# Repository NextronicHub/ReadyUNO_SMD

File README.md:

# ReadyUNO_SMD
## Description
READY-UNO is the best board to start your personal electronics projects, it is built upon the famous ARDUINO UNO, so it shares its simplicity and its flexibility. It contains also a BreadBoard with different interfaces of communication (SPI, UART, I2C and Serial communication) for easy development.
The READY-UNO can be programmed over a Serial Communication, using the ARDUINO IDE.
The READY-UNO can be powered through the barrel jack. The on-board power regulator can handle anything from 7 to 15VDC.
## Features
•	ATmega328 microcontroller with Optiboot (UNO) Bootloader                                                                         
•	Input voltage : 7 to 15V                                                                                                         
•	0-5V outputs                                                                                                                     
•	14 Digital I/O Pins (6 PWM outputs)                                                                                              
•	6 Analog Inputs                                                                                                                  
•	ISP Header                                                                                                                       
•	32k Flash Memory                                                                                                                 
•	16MHz Clock Speed                                                                                                                
•	All SMD Construction                                                                                                             
•	R3 Shield Compatible                                                                                                             
•	BreadBoard.                                                                                                                      
•	Red PCB.                                                                                                                         
•	I2C, UART and SPI.                                                                                                               
## Repository Contents

/Hardware - Design files (.brd, .sch)  
/Firmware - bootloader
/Documentation - datasheet and examples

## Product Versions

ReadyUNO-SMD-V1 first release

## License Information

The hardware is released under [Creative Commons ShareAlike 4.0 International](https://creativecommons.org/licenses/by-sa/4.0/).

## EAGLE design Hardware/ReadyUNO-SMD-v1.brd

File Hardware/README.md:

# Nextronic ReadyUNO_SMD Design Files
The .sch and .brd files are Eagle CAD schematic and PCB design files from Nextronic. Eagle PCB Design | Schematic Editor, Layout Editor & Autorouter can be found at http://www.autodesk.com/products/eagle.

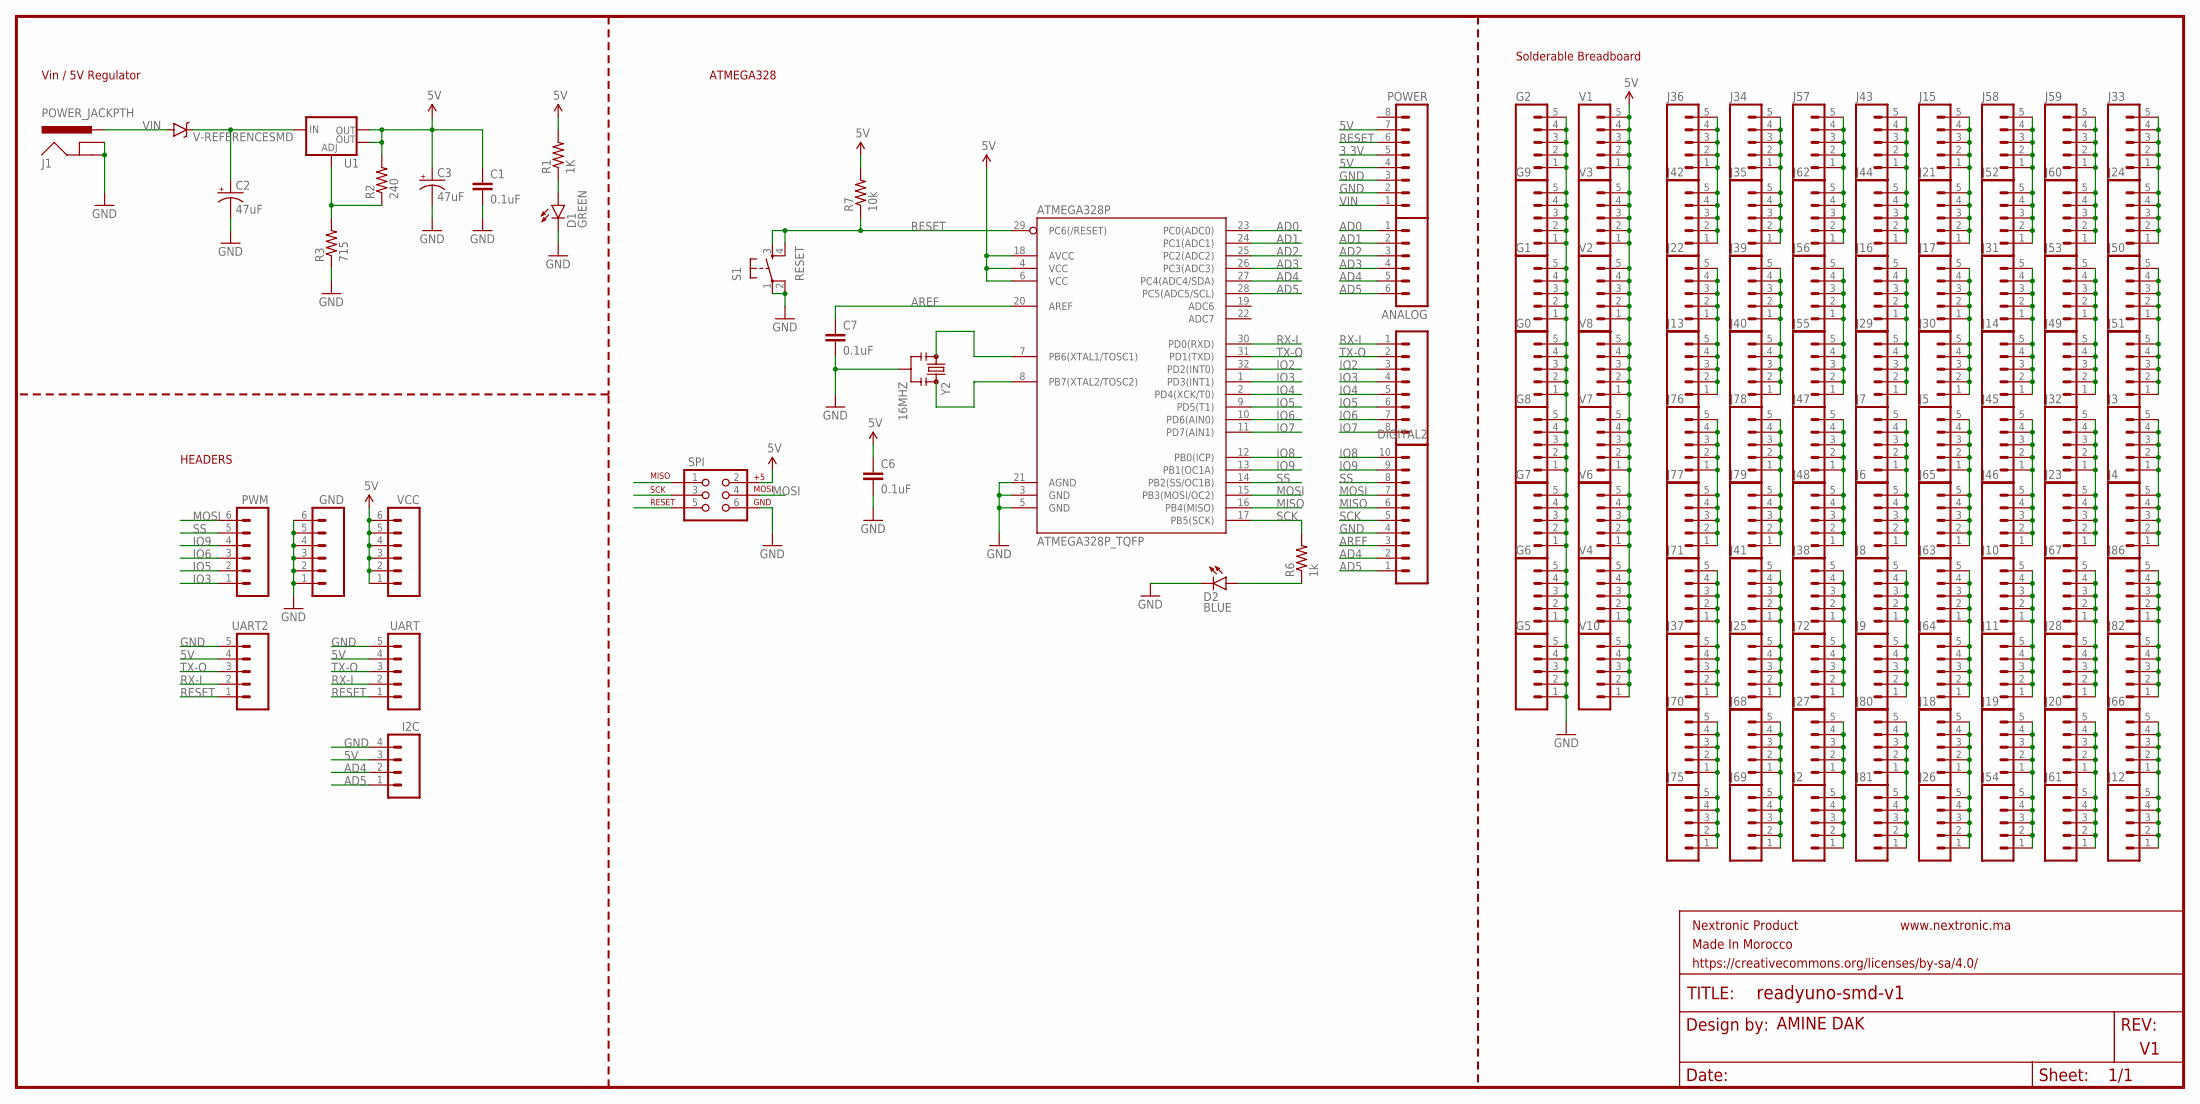
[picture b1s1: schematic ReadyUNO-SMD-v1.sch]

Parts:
ANALOG: M06SILK_FEMALE_PTH; 1X06
ATMEGA328P: ATMEGA328P_TQFP; TQFP32-08
C1, C6, C7: 0.1uF; 0603-CAP
C2, C3: 47uF; PANASONIC_C
D1: GREEN; LED-1206
D2: BLUE; LED-1206
DIGITAL: M08SILK_FEMALE_PTH; 1X08
DIGITAL2: M10SILK_FEMALE_PTH; 1X10
G0, G1, G2, G5, G6, G7, G8, G9: M05PTH; 1X05
GND: M06SILK_FEMALE_PTH; 1X06
I2C: M04PTH; 1X04
J1: POWER_JACKPTH; POWER_JACK_PTH
J2, J3, J4, J5, J6, J7, J8, J9, J10, J11, J12, J13, J14, J15, J16, J17, J18, J19, J20, J21, J22, J23, J24, J25, J26, J27, J28, J29, J30, J31, J32, J33, J34, J35, J36, J37, J38, J39, J40, J41, J42, J43, J44, J45, J46, J47, J48, J49, J50, J51, J52, J53, J54, J55, J56, J57, J58, J59, J60, J61, J62, J63, J64, J65, J66, J67, J68, J69, J70, J71, J72, J75, J76, J77, J78, J79, J80, J81, J82, J86: M05PTH; 1X05
POWER: M08SILK_FEMALE_PTH; 1X08
PWM: M06SILK_FEMALE_PTH; 1X06
R1: 1K; 0603-RES
R2: 240; 0603-RES
R3: 715; 0603-RES
R6: 1k; 0603-RES
R7: 10k; 0603-RES
S1: RESET; TACTILE-SWITCH-SMD
SPI: AVR_SPI_PRG_6NS; 2X3-NS
U1: V_REG_LM1117SOT223; SOT223
U$1: V-REFERENCESMD; SOT23-3
UART, UART2: M05PTH; 1X05
V1, V2, V3, V4, V6, V7, V8, V10: M05PTH; 1X05
VCC: M06SILK_FEMALE_PTH; 1X06
Y2: 16MHZ; RESONATOR-SMD

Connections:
3.3V: POWER.5
5V: ATMEGA328P.4 (VCC), ATMEGA328P.6 (VCC), ATMEGA328P.18 (AVCC), C1.1, C3.+, C6.1, I2C.3, POWER.4, POWER.7, R1.2, R2.2, R7.2, SPI.2, U1.2 (OUT), U1.4 (OUT), UART.4, UART2.4, V1.1, V1.2, V1.3, V1.4, V1.5, V2.1, V2.2, V2.3, V2.4, V2.5, V3.1, V3.2, V3.3, V3.4, V3.5, V4.1, V4.2, V4.3, V4.4, V4.5, V6.1, V6.2, V6.3, V6.4, V6.5, V7.1, V7.2, V7.3, V7.4, V7.5, V8.1, V8.2, V8.3, V8.4, V8.5, V10.1, V10.2, V10.3, V10.4, V10.5, VCC.1, VCC.2, VCC.3, VCC.4, VCC.5, VCC.6
AD0: ANALOG.1, ATMEGA328P.23 (PC0(ADC0))
AD1: ANALOG.2, ATMEGA328P.24 (PC1(ADC1))
AD2: ANALOG.3, ATMEGA328P.25 (PC2(ADC2))
AD3: ANALOG.4, ATMEGA328P.26 (PC3(ADC3))
AD4: ANALOG.5, ATMEGA328P.27 (PC4(ADC4/SDA)), DIGITAL2.2, I2C.2
AD5: ANALOG.6, ATMEGA328P.28 (PC5(ADC5/SCL)), DIGITAL2.1, I2C.1
AREF: ATMEGA328P.20 (AREF), C7.1, DIGITAL2.3
GND: ATMEGA328P.3 (GND), ATMEGA328P.5 (GND), ATMEGA328P.21 (AGND), C1.2, C2.-, C3.-, C6.2, C7.2, D1.C, D2.C, DIGITAL2.4, G0.1, G0.2, G0.3, G0.4, G0.5, G1.1, G1.2, G1.3, G1.4, G1.5, G2.1, G2.2, G2.3, G2.4, G2.5, G5.1, G5.2, G5.3, G5.4, G5.5, G6.1, G6.2, G6.3, G6.4, G6.5, G7.1, G7.2, G7.3, G7.4, G7.5, G8.1, G8.2, G8.3, G8.4, G8.5, G9.1, G9.2, G9.3, G9.4, G9.5, GND.1, GND.2, GND.3, GND.4, GND.5, GND.6, I2C.4, J1.GND, J1.GNDBREAK, POWER.2, POWER.3, R3.1, S1.1, S1.2, SPI.6, UART.5, UART2.5, Y2.2
IO2: ATMEGA328P.32 (PD2(INT0)), DIGITAL.3
IO3: ATMEGA328P.1 (PD3(INT1)), DIGITAL.4, PWM.1
IO4: ATMEGA328P.2 (PD4(XCK/T0)), DIGITAL.5
IO5: ATMEGA328P.9 (PD5(T1)), DIGITAL.6, PWM.2
IO6: ATMEGA328P.10 (PD6(AIN0)), DIGITAL.7, PWM.3
IO7: ATMEGA328P.11 (PD7(AIN1)), DIGITAL.8
IO8: ATMEGA328P.12 (PB0(ICP)), DIGITAL2.10
IO9: ATMEGA328P.13 (PB1(OC1A)), DIGITAL2.9, PWM.4
MISO: ATMEGA328P.16 (PB4(MISO)), DIGITAL2.6, SPI.1
MOSI: ATMEGA328P.15 (PB3(MOSI/OC2)), DIGITAL2.7, PWM.6, SPI.4
unnamed: R2.1, R3.2, U1.1 (ADJ)
unnamed: D2.A, R6.1
unnamed: C2.+, U1.3 (IN), U$1.1 (C)
unnamed: D1.A, R1.1
unnamed: J37.1, J37.2, J37.3, J37.4, J37.5, J71.1, J71.2, J71.3, J71.4, J71.5
unnamed: ATMEGA328P.7 (PB6(XTAL1/TOSC1)), Y2.1
unnamed: ATMEGA328P.8 (PB7(XTAL2/TOSC2)), Y2.3
unnamed: J3.1, J3.2, J3.3, J3.4, J3.5, J4.1, J4.2, J4.3, J4.4, J4.5
unnamed: J10.1, J10.2, J10.3, J10.4, J10.5, J11.1, J11.2, J11.3, J11.4, J11.5
unnamed: J76.1, J76.2, J76.3, J76.4, J76.5, J77.1, J77.2, J77.3, J77.4, J77.5
unnamed: J28.1, J28.2, J28.3, J28.4, J28.5, J67.1, J67.2, J67.3, J67.4, J67.5
unnamed: J25.1, J25.2, J25.3, J25.4, J25.5, J41.1, J41.2, J41.3, J41.4, J41.5
unnamed: J78.1, J78.2, J78.3, J78.4, J78.5, J79.1, J79.2, J79.3, J79.4, J79.5
unnamed: J82.1, J82.2, J82.3, J82.4, J82.5, J86.1, J86.2, J86.3, J86.4, J86.5
unnamed: J45.1, J45.2, J45.3, J45.4, J45.5, J46.1, J46.2, J46.3, J46.4, J46.5
unnamed: J47.1, J47.2, J47.3, J47.4, J47.5, J48.1, J48.2, J48.3, J48.4, J48.5
unnamed: J12.1, J12.2, J12.3, J12.4, J12.5, J66.1, J66.2, J66.3, J66.4, J66.5
unnamed: J20.1, J20.2, J20.3, J20.4, J20.5, J61.1, J61.2, J61.3, J61.4, J61.5
unnamed: J38.1, J38.2, J38.3, J38.4, J38.5, J72.1, J72.2, J72.3, J72.4, J72.5
unnamed: J24.1, J24.2, J24.3, J24.4, J24.5, J33.1, J33.2, J33.3, J33.4, J33.5
unnamed: J23.1, J23.2, J23.3, J23.4, J23.5, J32.1, J32.2, J32.3, J32.4, J32.5
unnamed: J49.1, J49.2, J49.3, J49.4, J49.5, J53.1, J53.2, J53.3, J53.4, J53.5
unnamed: J59.1, J59.2, J59.3, J59.4, J59.5, J60.1, J60.2, J60.3, J60.4, J60.5
unnamed: J14.1, J14.2, J14.3, J14.4, J14.5, J31.1, J31.2, J31.3, J31.4, J31.5
unnamed: J17.1, J17.2, J17.3, J17.4, J17.5, J30.1, J30.2, J30.3, J30.4, J30.5
unnamed: J52.1, J52.2, J52.3, J52.4, J52.5, J58.1, J58.2, J58.3, J58.4, J58.5
unnamed: J50.1, J50.2, J50.3, J50.4, J50.5, J51.1, J51.2, J51.3, J51.4, J51.5
unnamed: J16.1, J16.2, J16.3, J16.4, J16.5, J29.1, J29.2, J29.3, J29.4, J29.5
unnamed: J43.1, J43.2, J43.3, J43.4, J43.5, J44.1, J44.2, J44.3, J44.4, J44.5
unnamed: J15.1, J15.2, J15.3, J15.4, J15.5, J21.1, J21.2, J21.3, J21.4, J21.5
unnamed: J36.1, J36.2, J36.3, J36.4, J36.5, J42.1, J42.2, J42.3, J42.4, J42.5
unnamed: J13.1, J13.2, J13.3, J13.4, J13.5, J22.1, J22.2, J22.3, J22.4, J22.5
unnamed: J6.1, J6.2, J6.3, J6.4, J6.5, J7.1, J7.2, J7.3, J7.4, J7.5
unnamed: J8.1, J8.2, J8.3, J8.4, J8.5, J9.1, J9.2, J9.3, J9.4, J9.5
unnamed: J34.1, J34.2, J34.3, J34.4, J34.5, J35.1, J35.2, J35.3, J35.4, J35.5
unnamed: J39.1, J39.2, J39.3, J39.4, J39.5, J40.1, J40.2, J40.3, J40.4, J40.5
unnamed: J5.1, J5.2, J5.3, J5.4, J5.5, J65.1, J65.2, J65.3, J65.4, J65.5
unnamed: J63.1, J63.2, J63.3, J63.4, J63.5, J64.1, J64.2, J64.3, J64.4, J64.5
unnamed: J57.1, J57.2, J57.3, J57.4, J57.5, J62.1, J62.2, J62.3, J62.4, J62.5
unnamed: J55.1, J55.2, J55.3, J55.4, J55.5, J56.1, J56.2, J56.3, J56.4, J56.5
unnamed: J19.1, J19.2, J19.3, J19.4, J19.5, J54.1, J54.2, J54.3, J54.4, J54.5
unnamed: J80.1, J80.2, J80.3, J80.4, J80.5, J81.1, J81.2, J81.3, J81.4, J81.5
unnamed: J18.1, J18.2, J18.3, J18.4, J18.5, J26.1, J26.2, J26.3, J26.4, J26.5
unnamed: J70.1, J70.2, J70.3, J70.4, J70.5, J75.1, J75.2, J75.3, J75.4, J75.5
unnamed: J2.1, J2.2, J2.3, J2.4, J2.5, J27.1, J27.2, J27.3, J27.4, J27.5
unnamed: J68.1, J68.2, J68.3, J68.4, J68.5, J69.1, J69.2, J69.3, J69.4, J69.5
RESET: ATMEGA328P.29 (PC6(/RESET)), POWER.6, R7.1, S1.3, S1.4, SPI.5, UART.1, UART2.1
RX-I: ATMEGA328P.30 (PD0(RXD)), DIGITAL.1, UART.2, UART2.2
SCK: ATMEGA328P.17 (PB5(SCK)), DIGITAL2.5, R6.2, SPI.3
SS: ATMEGA328P.14 (PB2(SS/OC1B)), DIGITAL2.8, PWM.5
TX-O: ATMEGA328P.31 (PD1(TXD)), DIGITAL.2, UART.3, UART2.3
VIN: J1.PWR, POWER.1, U$1.2 (A)

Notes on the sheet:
Vin / 5V Regulator
ATMEGA328
HEADERS
Solderable Breadboard
AMINE DAK
Date:
Sheet:
REV:
TITLE:
Nextronic Product
Made In Morocco
https://creativecommons.org/licenses/by-sa/4.0/
Design by:
www.nextronic.ma

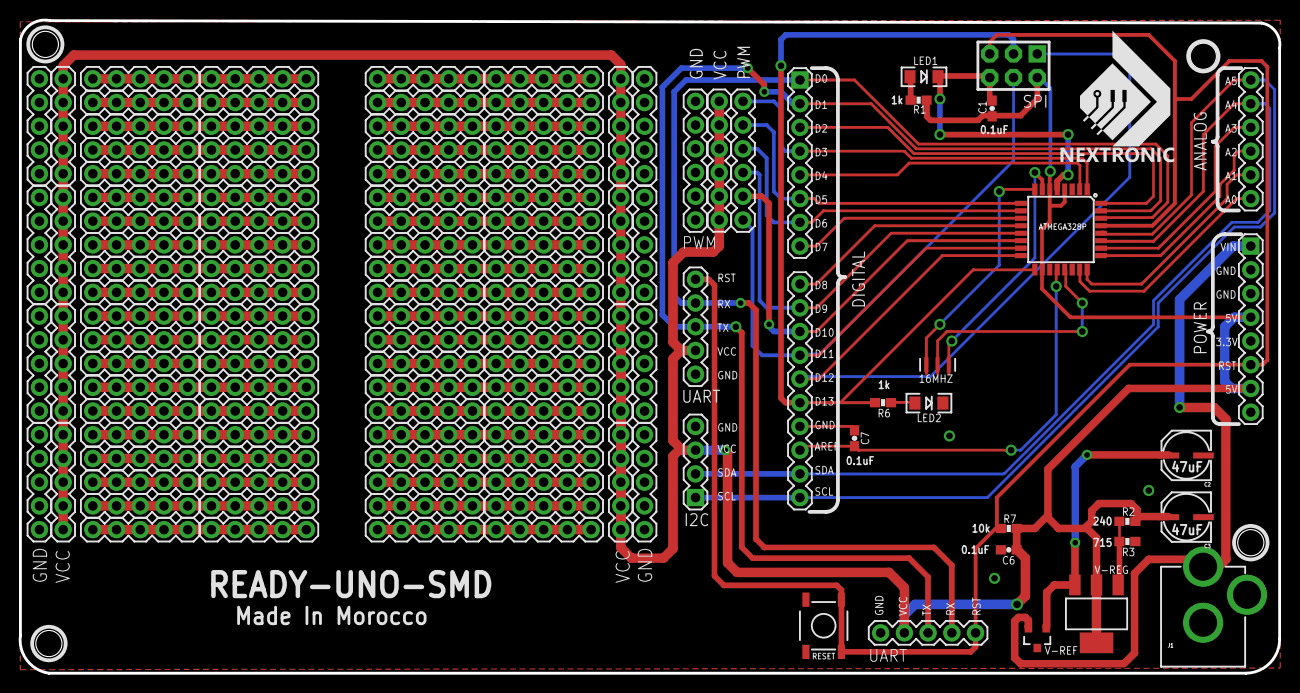
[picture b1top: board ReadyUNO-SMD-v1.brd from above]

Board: 2 copper layers, 134.8 x 69.9 mm, 125 parts (0 on the bottom side), 71 nets.

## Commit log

2017-01-23 READYUNO SMD Files
    The .sch and .brd files are Eagle CAD schematic and PCB design files from Nextronic. Eagle PCB Design | Schematic Editor, Layout Editor & Autorouter can be found at http://www.autodesk.com/products/e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
2017-01-23 Rename ReadyUNO_SMD.brd to Hardware/ReadyUNO_SMD.brd
2017-01-23 Rename ReadyUNO_SMD.sch to Hardware/ReadyUNO_SMD.sch
2017-01-23 Rename ReadyUno_bootloader.hex to Firmware/ReadyUno_bootloader.hex
2017-01-23 Rename ReadyUNO_SMD.brd to ReadyUNO-SMD-v1.brd
2017-01-23 Rename ReadyUNO_SMD.sch to ReadyUNO-SMD-v1.sch
2017-01-23 Rename Ready-UNO.brd to ReadyUNO_SMD.brd
2017-01-23 Rename Ready-UNO.sch to ReadyUNO-SMD-v1.sch

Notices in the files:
parts and their libraries:
SparkFun-Connectors: Licensing: Creative Commons ShareAlike 4.0 International - https://creativecommons.org/licenses/by-sa/4.0
